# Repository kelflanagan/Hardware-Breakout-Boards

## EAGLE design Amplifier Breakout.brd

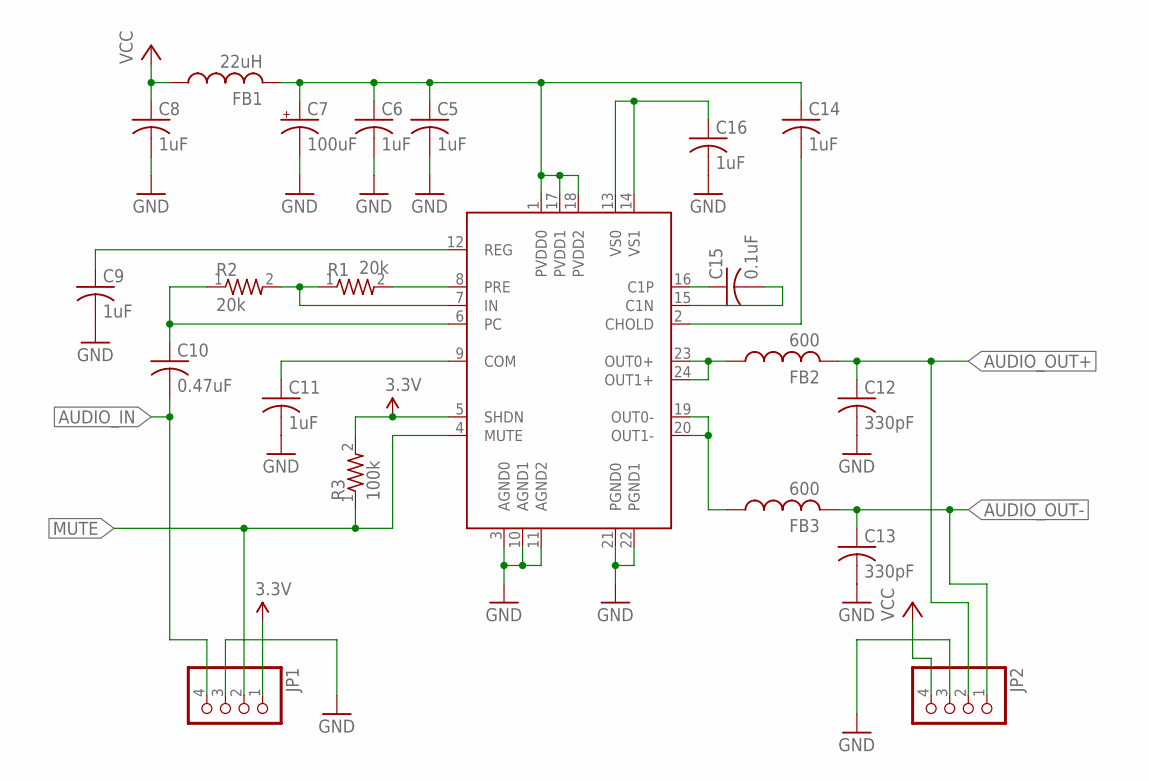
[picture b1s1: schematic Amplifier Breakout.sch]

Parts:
C5, C6, C8, C14: 1uF; FB-0805
C7: 100uF; CAP_F
C9, C11, C16: 1uF; 0603_RESISTOR
C10: 0.47uF; 0603_RESISTOR
C12, C13: 330pF; 0603_RESISTOR
C15: 0.1uF; 0603_RESISTOR
FB1: 22uH; FB-0805
FB2, FB3: 600; FB-0805
JP1, JP2: PINHD-1X4; 1X04
MAX1: MAX9737; TQFN24
R1, R2: 20k; 0603_RESISTOR
R3: 100k; 0603_RESISTOR

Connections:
3.3V: JP1.1, MAX1.5 (SHDN), R3.2
AUDIO_IN: C10.2, JP1.4
AUDIO_OUT+: C12.1, FB2.2, JP2.2
AUDIO_OUT-: C13.1, FB3.2, JP2.1
GND: C5.2, C6.2, C7.-, C8.2, C9.2, C11.2, C12.2, C13.2, C16.2, JP1.3, JP2.3, MAX1.3 (AGND0), MAX1.10 (AGND1), MAX1.11 (AGND2), MAX1.21 (PGND0), MAX1.22 (PGND1)
MUTE: JP1.2, MAX1.4 (MUTE), R3.1
unnamed: C9.1, MAX1.12 (REG)
unnamed: MAX1.8 (PRE), R1.2
unnamed: C5.1, C6.1, C7.+, C14.1, FB1.2, MAX1.1 (PVDD0), MAX1.17 (PVDD1), MAX1.18 (PVDD2)
unnamed: MAX1.7 (IN), R1.1, R2.2
unnamed: C10.1, MAX1.6 (PC), R2.1
unnamed: C11.1, MAX1.9 (COM)
unnamed: C14.2, MAX1.2 (CHOLD)
unnamed: C15.1, MAX1.16 (C1P)
unnamed: C15.2, MAX1.15 (C1N)
unnamed: C16.1, MAX1.13 (VS0), MAX1.14 (VS1)
unnamed: FB3.1, MAX1.19 (OUT0-), MAX1.20 (OUT1-)
unnamed: FB2.1, MAX1.23 (OUT0+), MAX1.24 (OUT1+)
VCC: C8.1, FB1.1, JP2.4

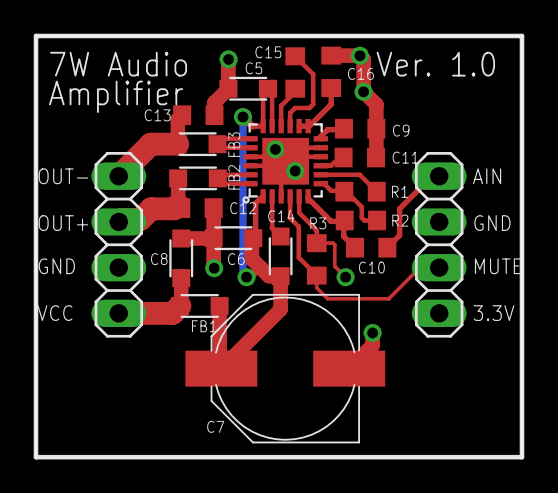
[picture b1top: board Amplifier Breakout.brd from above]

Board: 4 copper layers, 27.0 x 23.4 mm, 21 parts (0 on the bottom side), 19 nets.

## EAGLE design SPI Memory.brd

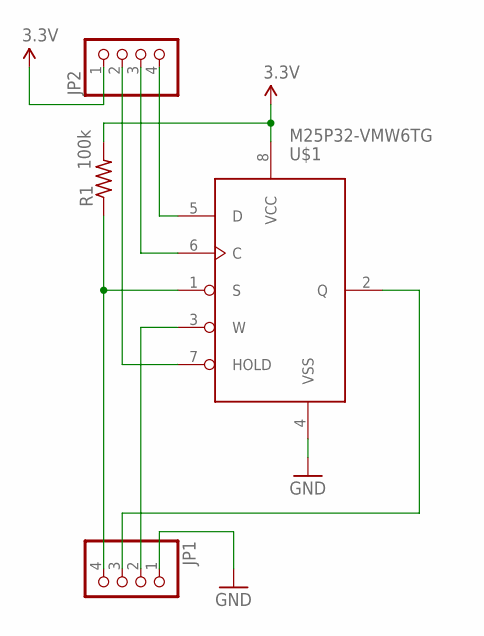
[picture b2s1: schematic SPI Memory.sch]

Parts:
JP1, JP2: PINHD-1X4; 1X04
R1: 100k; 0603_RESISTOR
U$1: M25P32-VMW6TG; SOIC8_W

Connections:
3.3V: JP2.1, R1.2, U$1.8 (VCC)
GND: JP1.1, U$1.4 (VSS)
unnamed: JP1.3, U$1.2 (Q)
unnamed: JP1.4, R1.1, U$1.1 (S)
unnamed: JP1.2, U$1.3 (W)
unnamed: JP2.2, U$1.7 (HOLD)
unnamed: JP2.3, U$1.6 (C)
unnamed: JP2.4, U$1.5 (D)

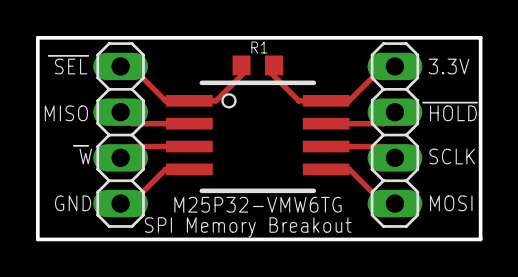
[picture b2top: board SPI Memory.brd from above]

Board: 2 copper layers, 24.6 x 11.2 mm, 4 parts (0 on the bottom side), 8 nets.

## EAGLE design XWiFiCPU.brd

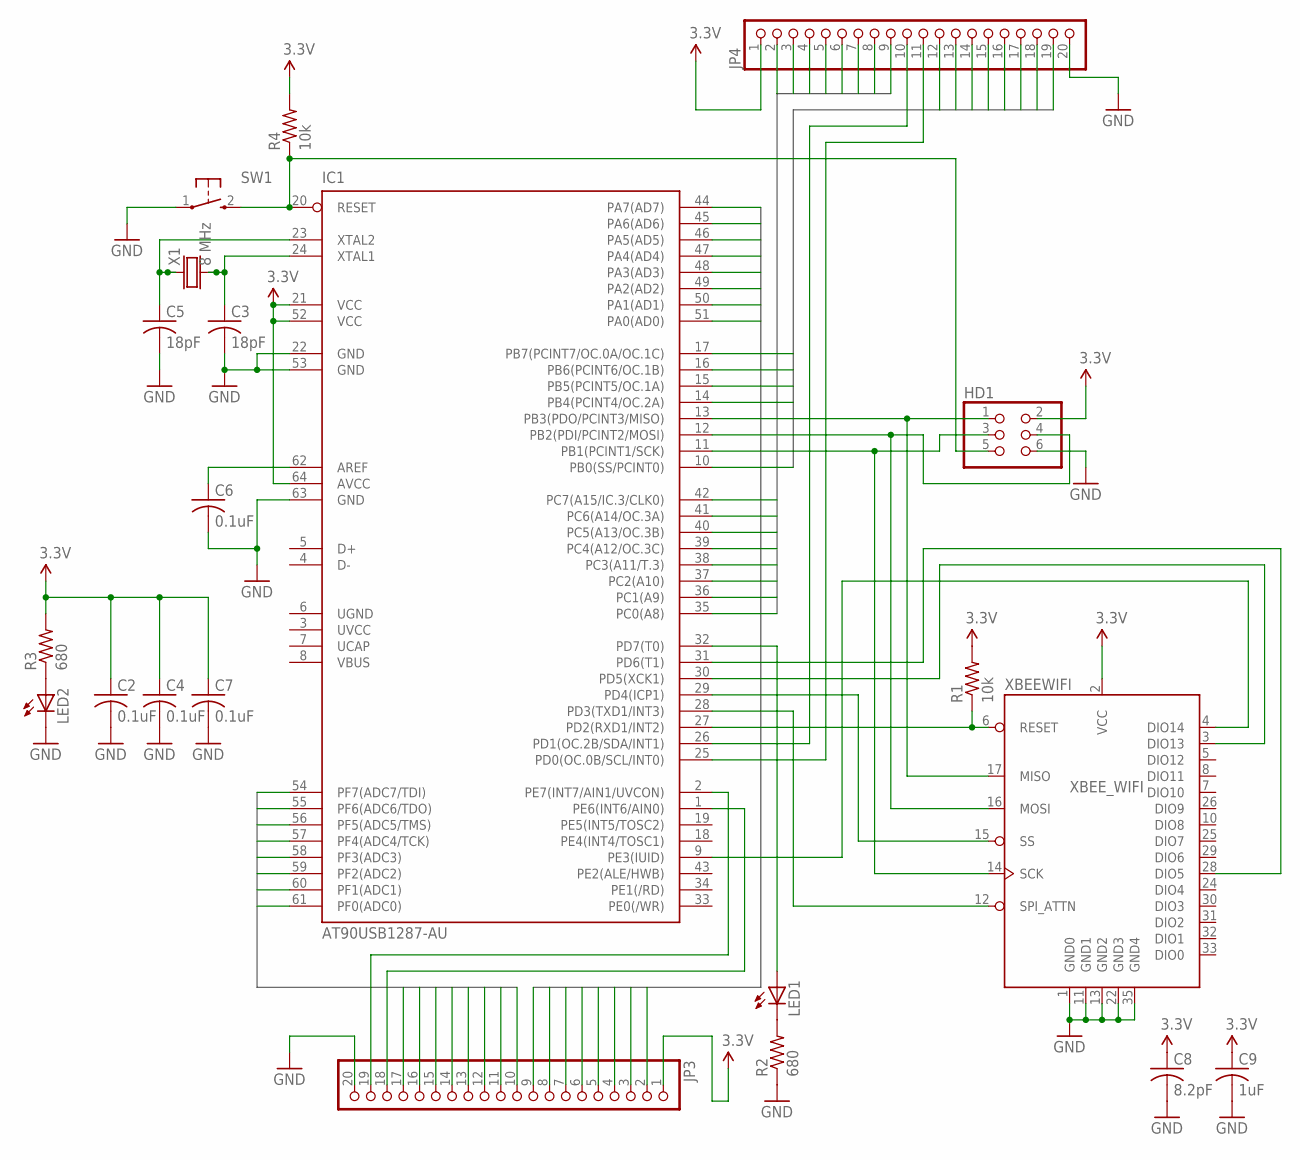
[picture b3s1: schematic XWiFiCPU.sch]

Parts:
C2, C4, C6, C7: 0.1uF; 0603_RESISTOR
C3, C5: 18pF; 0603_RESISTOR
C8: 8.2pF; 0603_RESISTOR
C9: 1uF; 0603_RESISTOR
HD1: HEADER2X3
IC1: AT90USB1287-AU; TQFP64
JP3, JP4: PINHD-1X20; 1X20
LED1, LED2: LEDCHIP-LED0603; CHIP-LED0603
R1, R4: 10k; 0603_RESISTOR
R2, R3: 680; 0603_RESISTOR
SW1: TAC-SWITCH
X1: 8 MHz; CRYSTAL_5X3
XBEEWIFI: XBEE_WIFI

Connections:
3.3V: C2.1, C4.1, C7.1, C8.1, C9.1, HD1.2, IC1.21 (VCC), IC1.52 (VCC), IC1.64 (AVCC), JP3.1, JP4.1, R1.2, R3.2, R4.2, XBEEWIFI.2 (VCC)
GND: C2.2, C3.2, C4.2, C5.2, C6.2, C7.2, C8.2, C9.2, HD1.6, IC1.22 (GND), IC1.53 (GND), IC1.63 (GND), JP3.20, JP4.20, LED2.C, R2.1, SW1.1, XBEEWIFI.1 (GND0), XBEEWIFI.11 (GND1), XBEEWIFI.13 (GND2), XBEEWIFI.22 (GND3), XBEEWIFI.35 (GND4)
unnamed: C5.1, IC1.23 (XTAL2), X1.1
unnamed: C3.1, IC1.24 (XTAL1), X1.2
unnamed: LED2.A, R3.1
unnamed: LED1.C, R2.2
unnamed: IC1.32 (PD7(T0)), LED1.A
unnamed: IC1.27 (PD2(RXD1/INT2)), R1.1, XBEEWIFI.6 (RESET)
unnamed: C6.1, IC1.62 (AREF)
unnamed: IC1.28 (PD3(TXD1/INT3)), XBEEWIFI.12 (SPI_ATTN)
unnamed: IC1.29 (PD4(ICP1)), XBEEWIFI.15 (SS)
unnamed: IC1.30 (PD5(XCK1)), XBEEWIFI.3 (DIO13)
unnamed: IC1.31 (PD6(T1)), XBEEWIFI.28 (DIO5)
unnamed: IC1.9 (PE3(IUID)), XBEEWIFI.4 (DIO14)
PA0: IC1.51 (PA0(AD0)), JP3.9
PA1: IC1.50 (PA1(AD1)), JP3.8
PA2: IC1.49 (PA2(AD2)), JP3.7
PA3: IC1.48 (PA3(AD3)), JP3.6
PA4: IC1.47 (PA4(AD4)), JP3.5
PA5: IC1.46 (PA5(AD5)), JP3.4
PA6: IC1.45 (PA6(AD6)), JP3.3
PA7: IC1.44 (PA7(AD7)), JP3.2
PB0: IC1.10 (PB0(SS/PCINT0)), JP4.19
PB1: HD1.3, IC1.11 (PB1(PCINT1/SCK)), JP4.18, XBEEWIFI.14 (SCK)
PB2: HD1.4, IC1.12 (PB2(PDI/PCINT2/MOSI)), JP4.17, XBEEWIFI.16 (MOSI)
PB3: HD1.1, IC1.13 (PB3(PDO/PCINT3/MISO)), JP4.16, XBEEWIFI.17 (MISO)
PB4: IC1.14 (PB4(PCINT4/OC.2A)), JP4.15
PB5: IC1.15 (PB5(PCINT5/OC.1A)), JP4.14
PB6: IC1.16 (PB6(PCINT6/OC.1B)), JP4.13
PB7: IC1.17 (PB7(PCINT7/OC.0A/OC.1C)), JP4.12
PC0: IC1.35 (PC0(A8)), JP4.9
PC1: IC1.36 (PC1(A9)), JP4.8
PC2: IC1.37 (PC2(A10)), JP4.7
PC3: IC1.38 (PC3(A11/T.3)), JP4.6
PC4: IC1.39 (PC4(A12/OC.3C)), JP4.5
PC5: IC1.40 (PC5(A13/OC.3B)), JP4.4
PC6: IC1.41 (PC6(A14/OC.3A)), JP4.3
PC7: IC1.42 (PC7(A15/IC.3/CLK0)), JP4.2
PD0: IC1.25 (PD0(OC.0B/SCL/INT0)), JP4.11
PD1: IC1.26 (PD1(OC.2B/SDA/INT1)), JP4.10
PE6: IC1.1 (PE6(INT6/AIN0)), JP3.18
PE7: IC1.2 (PE7(INT7/AIN1/UVCON)), JP3.19
PF0: IC1.61 (PF0(ADC0)), JP3.17
PF1: IC1.60 (PF1(ADC1)), JP3.16
PF2: IC1.59 (PF2(ADC2)), JP3.15
PF3: IC1.58 (PF3(ADC3)), JP3.14
PF4: IC1.57 (PF4(ADC4/TCK)), JP3.13
PF5: IC1.56 (PF5(ADC5/TMS)), JP3.12
PF6: IC1.55 (PF6(ADC6/TDO)), JP3.11
PF7: IC1.54 (PF7(ADC7/TDI)), JP3.10
RESET: HD1.5, IC1.20 (RESET), R4.1, SW1.2
UCAP: IC1.7 (UCAP)
UGND: IC1.6 (UGND)
UVCC: IC1.3 (UVCC)
VBUS: IC1.8 (VBUS)

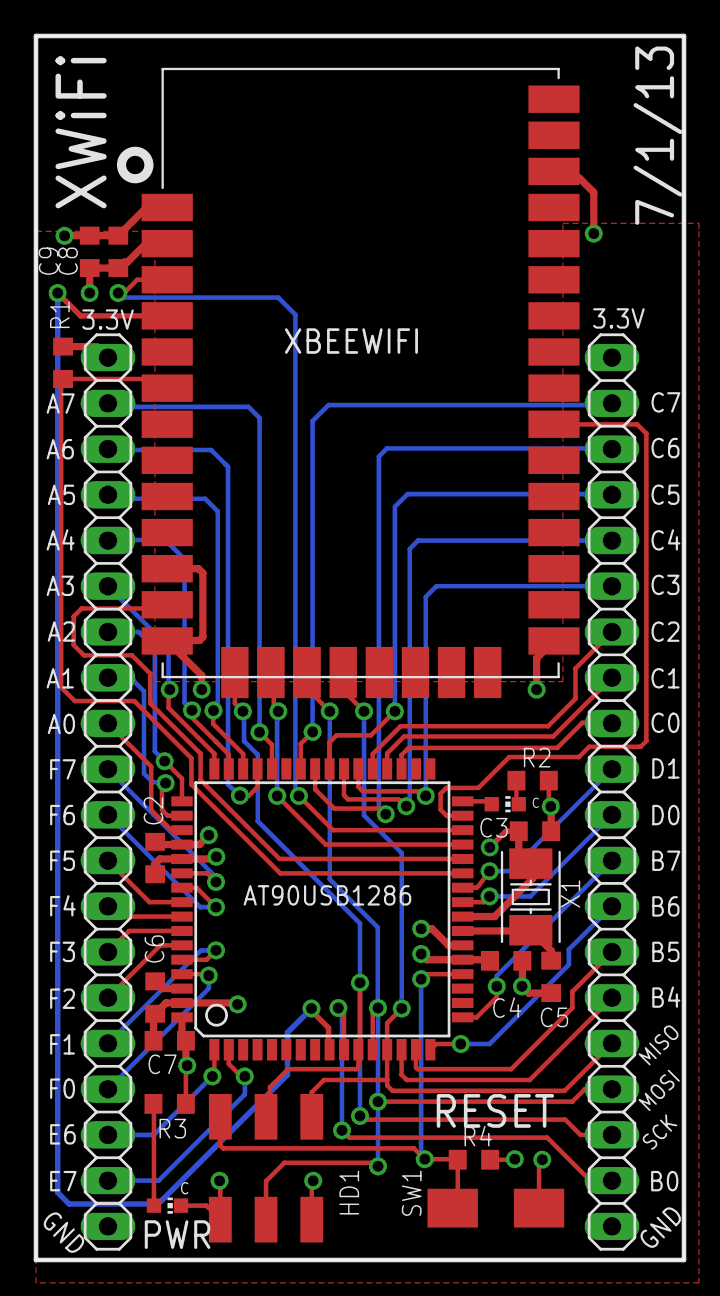
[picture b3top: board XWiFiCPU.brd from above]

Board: 4 copper layers, 36.0 x 68.0 mm, 21 parts (0 on the bottom side), 51 nets.

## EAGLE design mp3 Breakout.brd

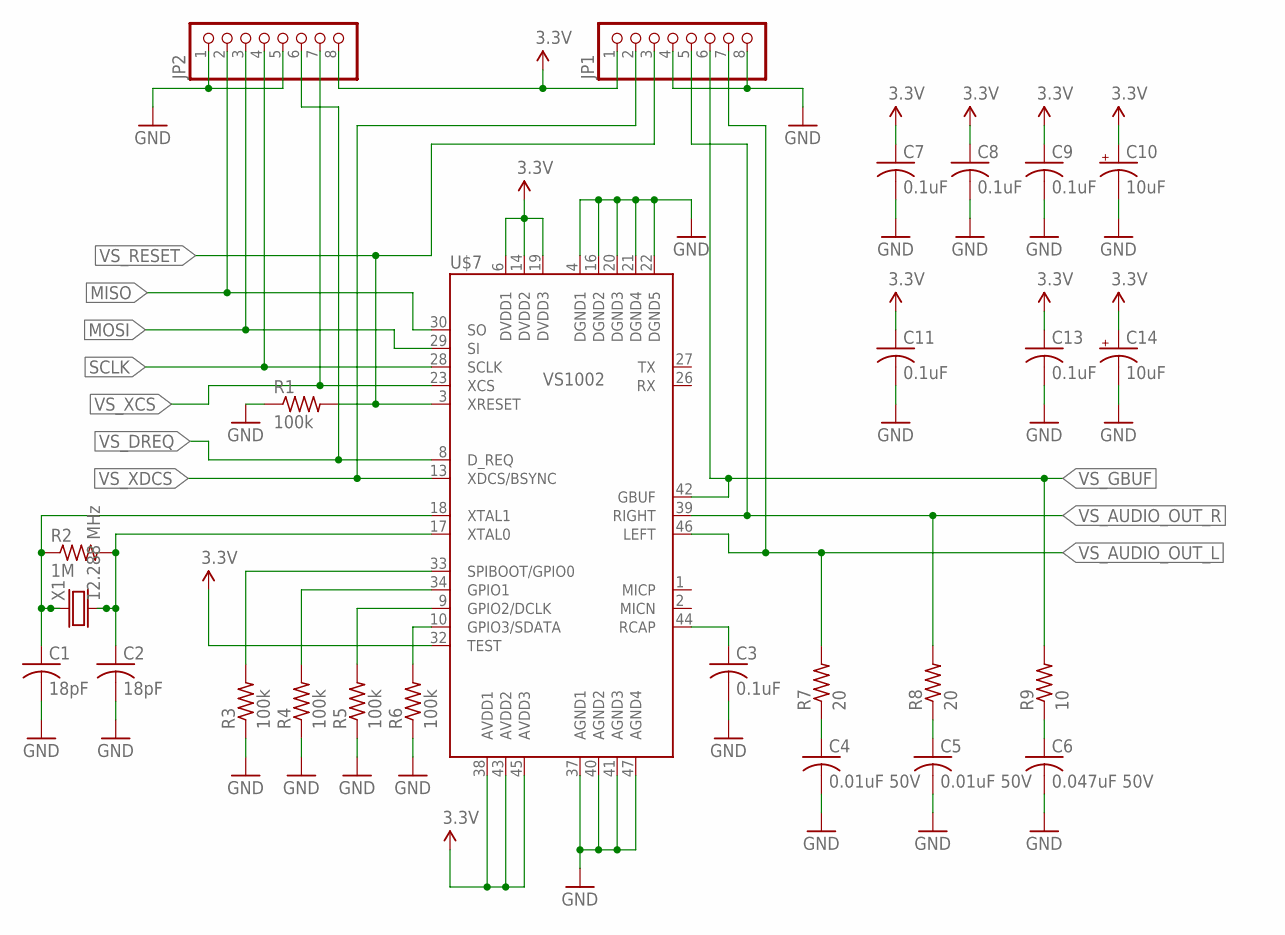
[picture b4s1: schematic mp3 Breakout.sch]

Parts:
C1, C2: 18pF; 0603_RESISTOR
C3, C7, C8, C9, C11, C13: 0.1uF; 0603_RESISTOR
C4, C5: 0.01uF 50V; 0603_RESISTOR
C6: 0.047uF 50V; 0603_RESISTOR
C10, C14: 10uF; CAP_B
JP1, JP2: PINHD-1X8; 1X08
R1, R3, R4, R5, R6: 100k; 0603_RESISTOR
R2: 1M; 0603_RESISTOR
R7, R8: 20; 0603_RESISTOR
R9: 10; 0603_RESISTOR
U$7: VS1002; LQFP-48
X1: 12.288 MHz; CRYSTAL_5X3

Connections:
3.3V: C7.1, C8.1, C9.1, C10.+, C11.1, C13.1, C14.+, JP1.1, JP2.8, U$7.6 (DVDD1), U$7.14 (DVDD2), U$7.19 (DVDD3), U$7.32 (TEST), U$7.38 (AVDD1), U$7.43 (AVDD2), U$7.45 (AVDD3)
GND: C1.2, C2.2, C3.2, C4.2, C5.2, C6.2, C7.2, C8.2, C9.2, C10.-, C11.2, C13.2, C14.-, JP1.4, JP1.8, JP2.1, JP2.5, R1.1, R3.1, R4.1, R5.1, R6.1, U$7.4 (DGND1), U$7.16 (DGND2), U$7.20 (DGND3), U$7.21 (DGND4), U$7.22 (DGND5), U$7.37 (AGND1), U$7.40 (AGND2), U$7.41 (AGND3), U$7.47 (AGND4)
MISO: JP2.2, U$7.30 (SO)
MOSI: JP2.3, U$7.29 (SI)
unnamed: C1.1, R2.1, U$7.18 (XTAL1), X1.1
unnamed: C2.1, R2.2, U$7.17 (XTAL0), X1.2
unnamed: C3.1, U$7.44 (RCAP)
unnamed: R6.2, U$7.10 (GPIO3/SDATA)
unnamed: R5.2, U$7.9 (GPIO2/DCLK)
unnamed: R4.2, U$7.34 (GPIO1)
unnamed: R3.2, U$7.33 (SPIBOOT/GPIO0)
unnamed: C4.1, R7.1
unnamed: C5.1, R8.1
unnamed: C6.1, R9.1
SCLK: JP2.4, U$7.28 (SCLK)
VS_AUDIO_OUT_L: JP1.7, R7.2, U$7.46 (LEFT)
VS_AUDIO_OUT_R: JP1.5, R8.2, U$7.39 (RIGHT)
VS_DREQ: JP2.6, U$7.8 (D_REQ)
VS_GBUF: JP1.6, R9.2, U$7.42 (GBUF)
VS_RESET: JP1.3, R1.2, U$7.3 (XRESET)
VS_XCS: JP2.7, U$7.23 (XCS)
VS_XDCS: JP1.2, U$7.13 (XDCS/BSYNC)

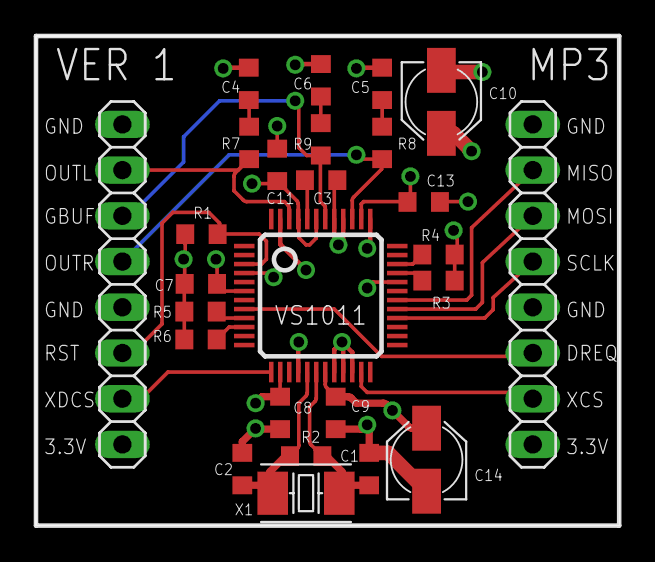
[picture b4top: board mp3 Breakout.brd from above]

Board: 4 copper layers, 32.4 x 27.2 mm, 26 parts (0 on the bottom side), 22 nets.

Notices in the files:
parts and their libraries:
SparkFun-Aesthetics: Licensing: CC v3.0 Share-Alike You are welcome to use this library for commercial purposes.
